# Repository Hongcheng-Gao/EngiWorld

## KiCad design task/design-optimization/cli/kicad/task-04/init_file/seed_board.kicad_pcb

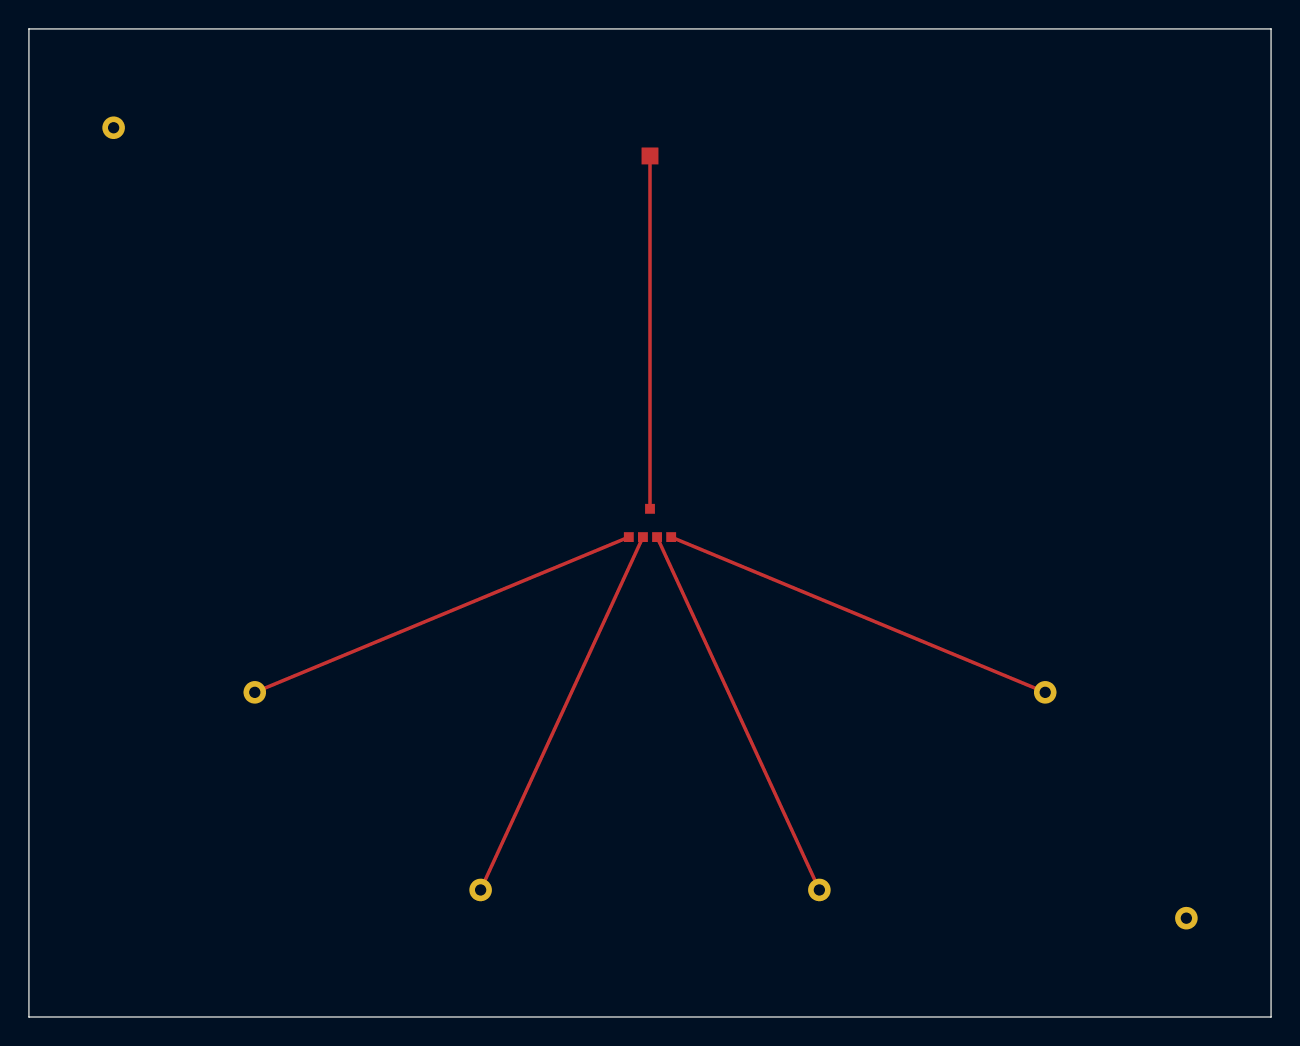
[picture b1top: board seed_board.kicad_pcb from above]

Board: 2 copper layers, 88.0 x 70.0 mm, 8 parts (0 on the bottom side), 5 nets.

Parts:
C1: C1
J1: J1
J2: J2
TP1, TP2, TP3, TP4: POGO_TEST
U1: U1

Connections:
C1_U1: C1.1, U1.5
TP1_U1: TP1.1, U1.1
TP2_U1: TP2.1, U1.2
TP3_U1: TP3.1, U1.3
TP4_U1: TP4.1, U1.4

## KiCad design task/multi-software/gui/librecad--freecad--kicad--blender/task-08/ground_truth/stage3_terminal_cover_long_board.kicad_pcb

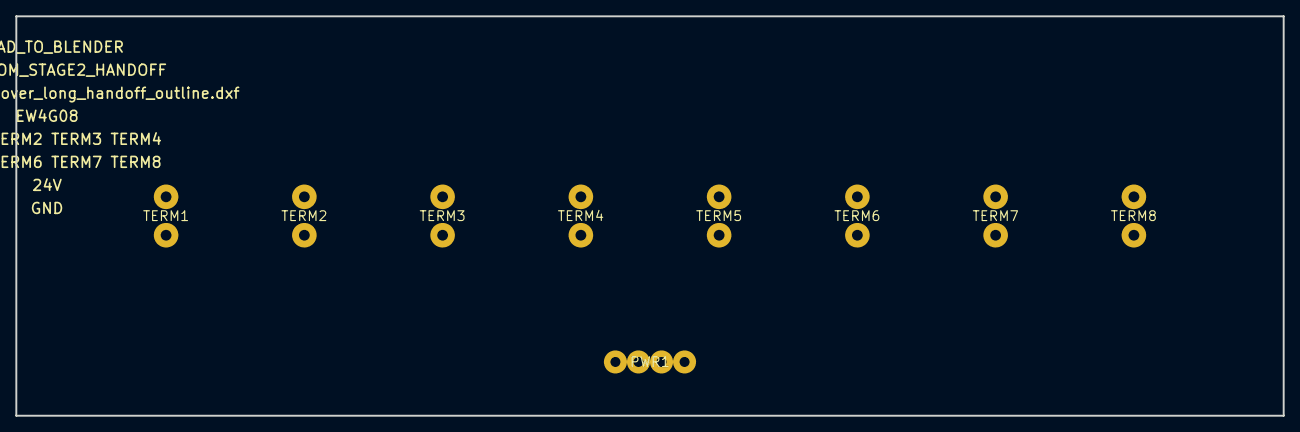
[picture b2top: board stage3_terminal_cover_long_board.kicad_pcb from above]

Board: 2 copper layers, 165.0 x 52.0 mm, 9 parts (0 on the bottom side), 2 nets, no tracks yet.

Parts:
PWR1: 24V GND power input
TERM1: 2-pin terminal channel 1
TERM2: 2-pin terminal channel 2
TERM3: 2-pin terminal channel 3
TERM4: 2-pin terminal channel 4
TERM5: 2-pin terminal channel 5
TERM6: 2-pin terminal channel 6
TERM7: 2-pin terminal channel 7
TERM8: 2-pin terminal channel 8

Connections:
24V: PWR1.1, PWR1.2
GND: PWR1.3, PWR1.4, TERM1.2, TERM2.2, TERM3.2, TERM4.2, TERM5.2, TERM6.2, TERM7.2, TERM8.2

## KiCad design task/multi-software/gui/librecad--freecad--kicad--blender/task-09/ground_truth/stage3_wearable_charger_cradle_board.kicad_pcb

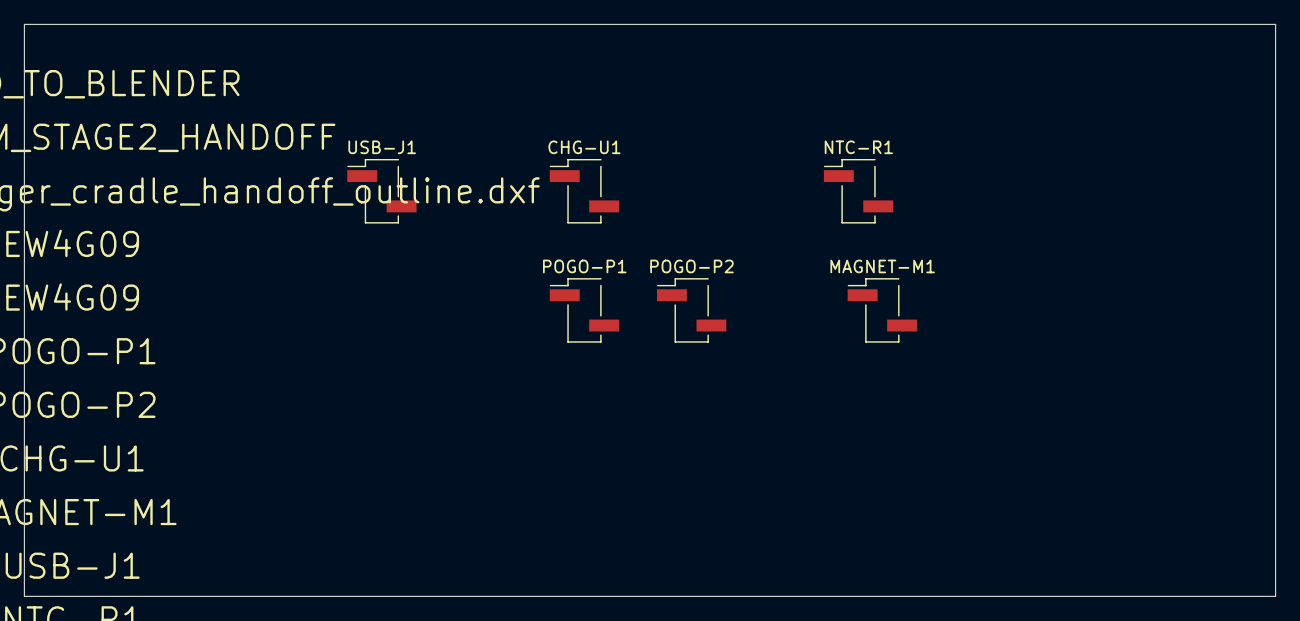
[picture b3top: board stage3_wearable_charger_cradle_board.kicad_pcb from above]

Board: 2 copper layers, 105.0 x 48.0 mm, 6 parts (0 on the bottom side), 2 nets, no tracks yet.

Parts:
CHG-U1: CHARGER_IC; PinHeader_1x02_P2.54mm_Vertical_SMD_Pin1Left
MAGNET-M1: MAGNET_MARKER; PinHeader_1x02_P2.54mm_Vertical_SMD_Pin1Left
NTC-R1: NTC_SENSOR; PinHeader_1x02_P2.54mm_Vertical_SMD_Pin1Left
POGO-P1: POGO_POS_CONTACT; PinHeader_1x02_P2.54mm_Vertical_SMD_Pin1Left
POGO-P2: POGO_NEG_CONTACT; PinHeader_1x02_P2.54mm_Vertical_SMD_Pin1Left
USB-J1: USB_INPUT; PinHeader_1x02_P2.54mm_Vertical_SMD_Pin1Left

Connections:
GND: MAGNET-M1.1, MAGNET-M1.2, NTC-R1.2, POGO-P1.2, POGO-P2.2, USB-J1.2
VBUS: CHG-U1.1, USB-J1.1

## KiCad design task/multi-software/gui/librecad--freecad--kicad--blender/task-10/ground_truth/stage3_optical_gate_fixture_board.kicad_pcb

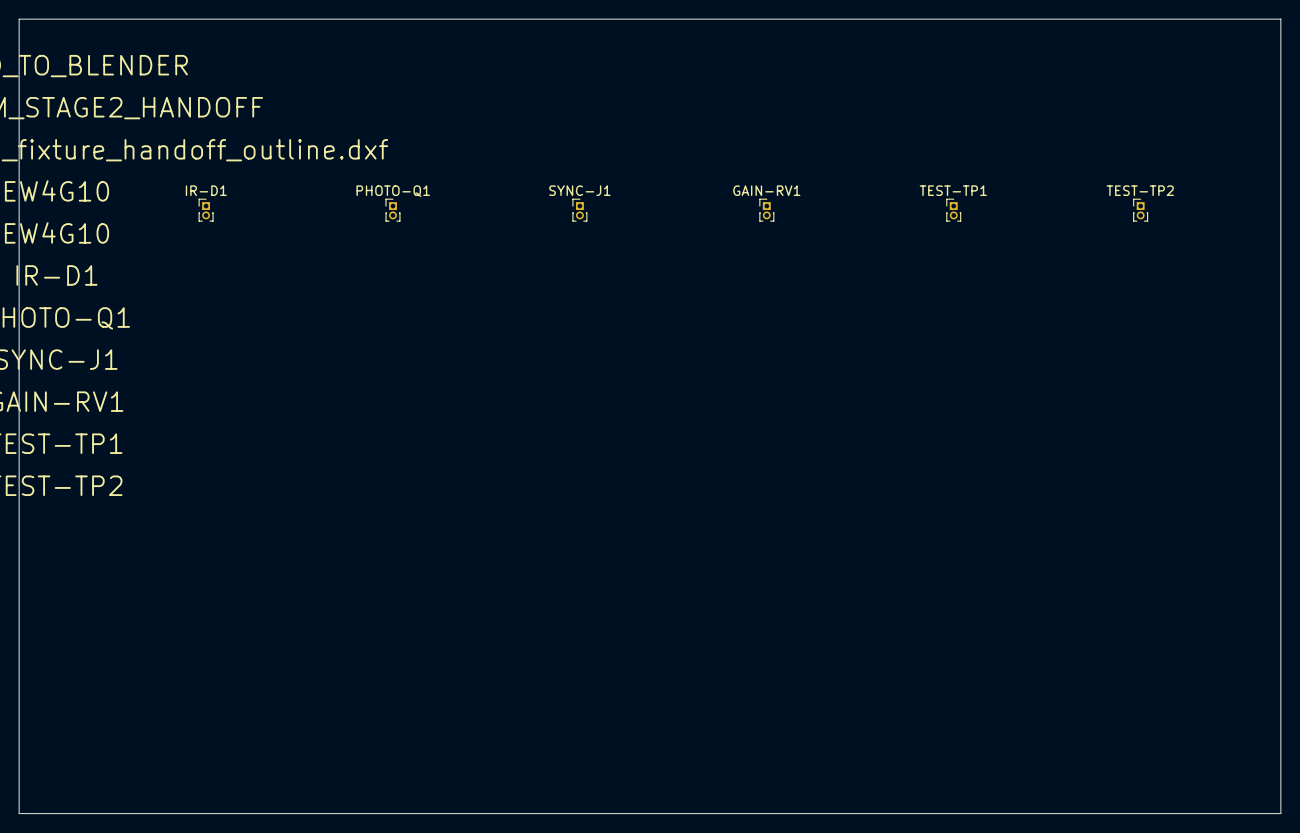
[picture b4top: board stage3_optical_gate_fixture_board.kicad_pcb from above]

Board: 2 copper layers, 135.0 x 85.0 mm, 6 parts (0 on the bottom side), 2 nets, no tracks yet.

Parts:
GAIN-RV1: GAIN-RV1; PinHeader_1x02_P1.00mm_Vertical
IR-D1: IR-D1; PinHeader_1x02_P1.00mm_Vertical
PHOTO-Q1: PHOTO-Q1; PinHeader_1x02_P1.00mm_Vertical
SYNC-J1: SYNC-J1; PinHeader_1x02_P1.00mm_Vertical
TEST-TP1: TEST-TP1; PinHeader_1x02_P1.00mm_Vertical
TEST-TP2: TEST-TP2; PinHeader_1x02_P1.00mm_Vertical

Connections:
GND: GAIN-RV1.2, PHOTO-Q1.1, PHOTO-Q1.2, SYNC-J1.2, TEST-TP1.2, TEST-TP2.2
IR_DRIVE: IR-D1.2, SYNC-J1.1
